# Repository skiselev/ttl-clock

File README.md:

# TTL Clock
74xx ICs Based Digital Clock

## Introduction
I got a bit tired from soldering SMD components, writing firmware, (and also observing people building vintage-looking Nixie clocks using modern microcontrollers). And recently when cleaning my parts boxes I found several 74LS47 7-segment decoders, some 74LS90 decade counters, and MAN1A 7-segment displays. So I thought, why not to build a nice little clock using these components.

## Assembly Instructions

[Assembly Instructions](Assembly_Instructions.md)

## Design Overview
Please refer to the schematic file in the Design Files section below.

The clock uses a 32768 Hz quartz crystal (X1) and 74HC4060 counter/divider IC (U1) to generate 2 Hz signal. This signal is divided further by 2 using a part of 74LS90 counter (U6). The obtained 1 Hz signal is fed to two 74LS90 counters (U11 and U12) that count seconds. The seconds reset circuit implemented using two 74LS00 NAND gates (U4A and U4B). This circuit resets both seconds and tens of seconds counters when they reach "60" or when "SECONDS" switch (SW1) is pressed, allowing seconds adjustment.

The most significant bit of tens of seconds counter is fed to the minutes counter implemented using two 74LS90 counters (U13 and U14) through a multiplexer built from three 74LS00 NAND gates (U2C, U2D, U4D). The multiplexer selects between this "one pulse per minute" signal and the 2 Hz signal allowing setting up minutes. Two additional 74LS00 NAND gates (U2A and U2B) implement an RS flip-flop used to de-bounce "MINUTES" switch (SW2). The tens of the minutes 74LS90 counter (U14) is wired so that it resets itself when it reaches count of "6", so that minutes wrap around at "60".

Similarly to minutes, the most significant bit of tens of minutes is fed to the hours counter implemented using two 74LS90 counters (U15 and U16) through a multiplexer built from three 74LS00 NAND gates (U3C, U3D, U4C). The multiplexer selects between this "one pulse per hour" signal and the 2 Hz signal allowing setting up hours. Two additional 74LS00 NAND gates (U3A and U3B) implement an RS flip-flop used to de-bounce "HOURS" switch (SW3). Both hours counters are wired in such a way that they will reset themselves once they reach the count of "24".

Six 74LS47 7-segment decoders (U5 - U10) are used to decode the binary outputs of the counters and 7-segment displays (U17 - U19) display the result in human readable 24-hours time format.

## Design Files

[Schematic - Version 1.1](KiCad/TTL_Clock-Schematic-1.1.pdf)

[Board - Version 1.1](KiCad/TTL_Clock-Board-1.1.pdf)

## Bill of Materials

[TTL Clock V1.1 project on Mouser.com](https://www.mouser.com/ProjectManager/ProjectDetail.aspx?AccessID=75baf81884) - View and order all components except of the PCB.

[TTL Clock Version 1.1 project on OSH Park](https://oshpark.com/shared_projects/GOxwvQh1) - Order PCBs.

Component type     | Reference | Description                                 | Quantity | Possible sources and notes
------------------ | --------- | ------------------------------------------- | -------- | --------------------------
PCB                |           | TTL Clock V1.1 Printed Circuit Board        | 1        | Order from [OSH Park](https://oshpark.com/shared_projects/GOxwvQh1) or another PCB manufacturer using provided KiCad or Gerber files
Stand              |           | 3D printed stand for the clock              | 1        | (Optional) Print on a 3D printer using [stand.stl](printed_parts/stand.stl). Thanks to Michael K. for designing this stand.
Screw              |           | M3 x 6mm screw                              | 2        | (Optional)
Capacitor          | C1 - C16  | 0.1uF, 50V, multilayer ceramic capacitor, axial | 16   | Mouser: [594-A104K15X7RF5UAA](https://www.mouser.com/ProductDetail/594-A104K15X7RF5UAA)
Capacitor          | C17       | 100uF, 25V, electrolytic capacitor, radial, 6.3 mm diameter | 1 | Mouser: [710-860040473003](https://www.mouser.com/ProductDetail/710-860040473003)
Capacitor          | C18       | 12pF, 50V, multilayer ceramic capacitor, 5.08 mm lead spacing | 1 | Mouser: [810-FK28C0G1H120J](https://www.mouser.com/ProductDetail/810-FK28C0G1H120J)
Trimmer Capacitor  | C19       | 5-30pF, trimmer capacitor, 5 mm lead spacing | 1       | Mouser: [659-GKG20015](https://www.mouser.com/ProductDetail/659-GKG20015)
LED                | D1 - D4   | 3 mm LED, same color as U17 - U19            | 4       | Mouser: [859-LTL-4221](https://www.mouser.com/ProductDetail/859-LTL-4221) (red, 623 nm) [859-LTL-4211](https://www.mouser.com/ProductDetail/859-LTL-4211) (red, 697 nm, 2.5 mcd), [859-LTL-4231](https://www.mouser.com/ProductDetail/859-LTL-4231) (green, 565 nm)
Connector          | P1        | DC Power Jack                               | 1        | Mouser: [806-KLDX-0202-A](https://www.mouser.com/ProductDetail/806-KLDX-0202-A)
Resistor           | R1 - R5   | 4.7 kOhm, 1/4 W                             | 5        | Mouser: [588-OK4725E-R52](https://www.mouser.com/ProductDetail/588-OK4725E-R52), [603-MFR25SFRF52-4K7](https://www.mouser.com/ProductDetail/603-MFR25SFRF52-4K7)
Resistor           | R6        | 330 kOhm, 1/4 W                             | 1        | Mouser: [588-OK3345E-R52](https://www.mouser.com/ProductDetail/588-OK3345E-R52)
Resistor           | R7        | 15 MOhm, 1/4 W                              | 1        | Mouser: [660-CF1/4C156J](https://www.mouser.com/ProductDetail/660-CF1-4C156J)
Resistor Array     | RR1 - RR6 | 470 Ohm, 8 isolated resistors, 16 pin DIP   | 6        | Mouser: [652-4116R-1LF-470](https://www.mouser.com/ProductDetail/652-4116R-1LF-470), [652-4116R-1-470](https://www.mouser.com/ProductDetail/652-4116R-1-470), or 46 x 470 ohm discrete resistors
Switch             | SW1 - SW3 | SPDT momentary switch, Omron D2F            | 3        | Mouser: [612-SS0750301F040P1A](https://www.mouser.com/ProductDetail/612-SS0750301F040P1A), [653-D2F-01L](https://www.mouser.com/ProductDetail/653-D2F-01L)
Integrated Circuit | U1        | 14-stage binary counter with oscillator, 74HC4060 | 1  | Mouser: [595-SN74HC4060N](https://www.mouser.com/ProductDetail/595-SN74HC4060N), [595-CD74HCT4060E](https://www.mouser.com/ProductDetail/595-CD74HCT4060E), [595-CD74HC4060E](https://www.mouser.com/ProductDetail/595-CD74HC4060E)
Integrated Circuit | U2 - U4   | Quad 4-input NAND gate, 74LS00              | 3        | Mouser: [595-SN74LS00N](https://www.mouser.com/ProductDetail/595-SN74LS00N), [595-SN74LS00NE4](https://www.mouser.com/ProductDetail/595-SN74LS00NE4)
Integrated Circuit | U5 - U10  | BCD to 7-segment decoder, 74LS47 or 74LS247 | 6        | Mouser: [595-SN74LS47N](https://www.mouser.com/ProductDetail/595-SN74LS47N), [595-SN74LS47NE4](https://www.mouser.com/ProductDetail/SN74LS47NE4), [595-SN74LS247N](https://www.mouser.com/ProductDetail/595-SN74LS247N), [595-SN74LS247NE4](https://www.mouser.com/ProductDetail/595-SN74LS247NE4)
Integrated Circuit | U11 - U16 | Decade counter, 74LS90                      | 6        | Mouser: [595-SN74LS90N](https://www.mouser.com/ProductDetail/595-SN74LS90N), [595-SN74LS90NE4](https://www.mouser.com/ProductDetail/595-SN74LS90NE4)
LED Display        | U17 - U19 | 7-segment LED display, 2 digits, common anode | 3      | Mouser: [859-LTD-6910HR](https://www.mouser.com/ProductDetail/859-LTD-6910HR) (red, 623 nm), [859-LTD-6410G](https://www.mouser.com/ProductDetail/859-LTD-6410G) (green, 569 nm)
Crystal Resonator  | X1        | 32768 Hz, 12.5pF load capacitance, tuning fork | 1     | Mouser: [695-CFS-20632768EZBB](https://www.mouser.com/ProductDetail/695-CFS-20632768EZBB), [815-AB26T-32.768KHZ](https://www.mouser.com/ProductDetail/815-AB26T-32.768KHZ)
Power Supply       |           | 5 V, 550 mA                                 | 1        | Mouser: [490-SWI3-5-N-P5](https://www.mouser.com/ProductDetail/490-SWI3-5-N-P5) (US plug), [490-SWI3-5-E-P5](https://www.mouser.com/ProductDetail/490-SWI3-5-E-P5) (EU plug)

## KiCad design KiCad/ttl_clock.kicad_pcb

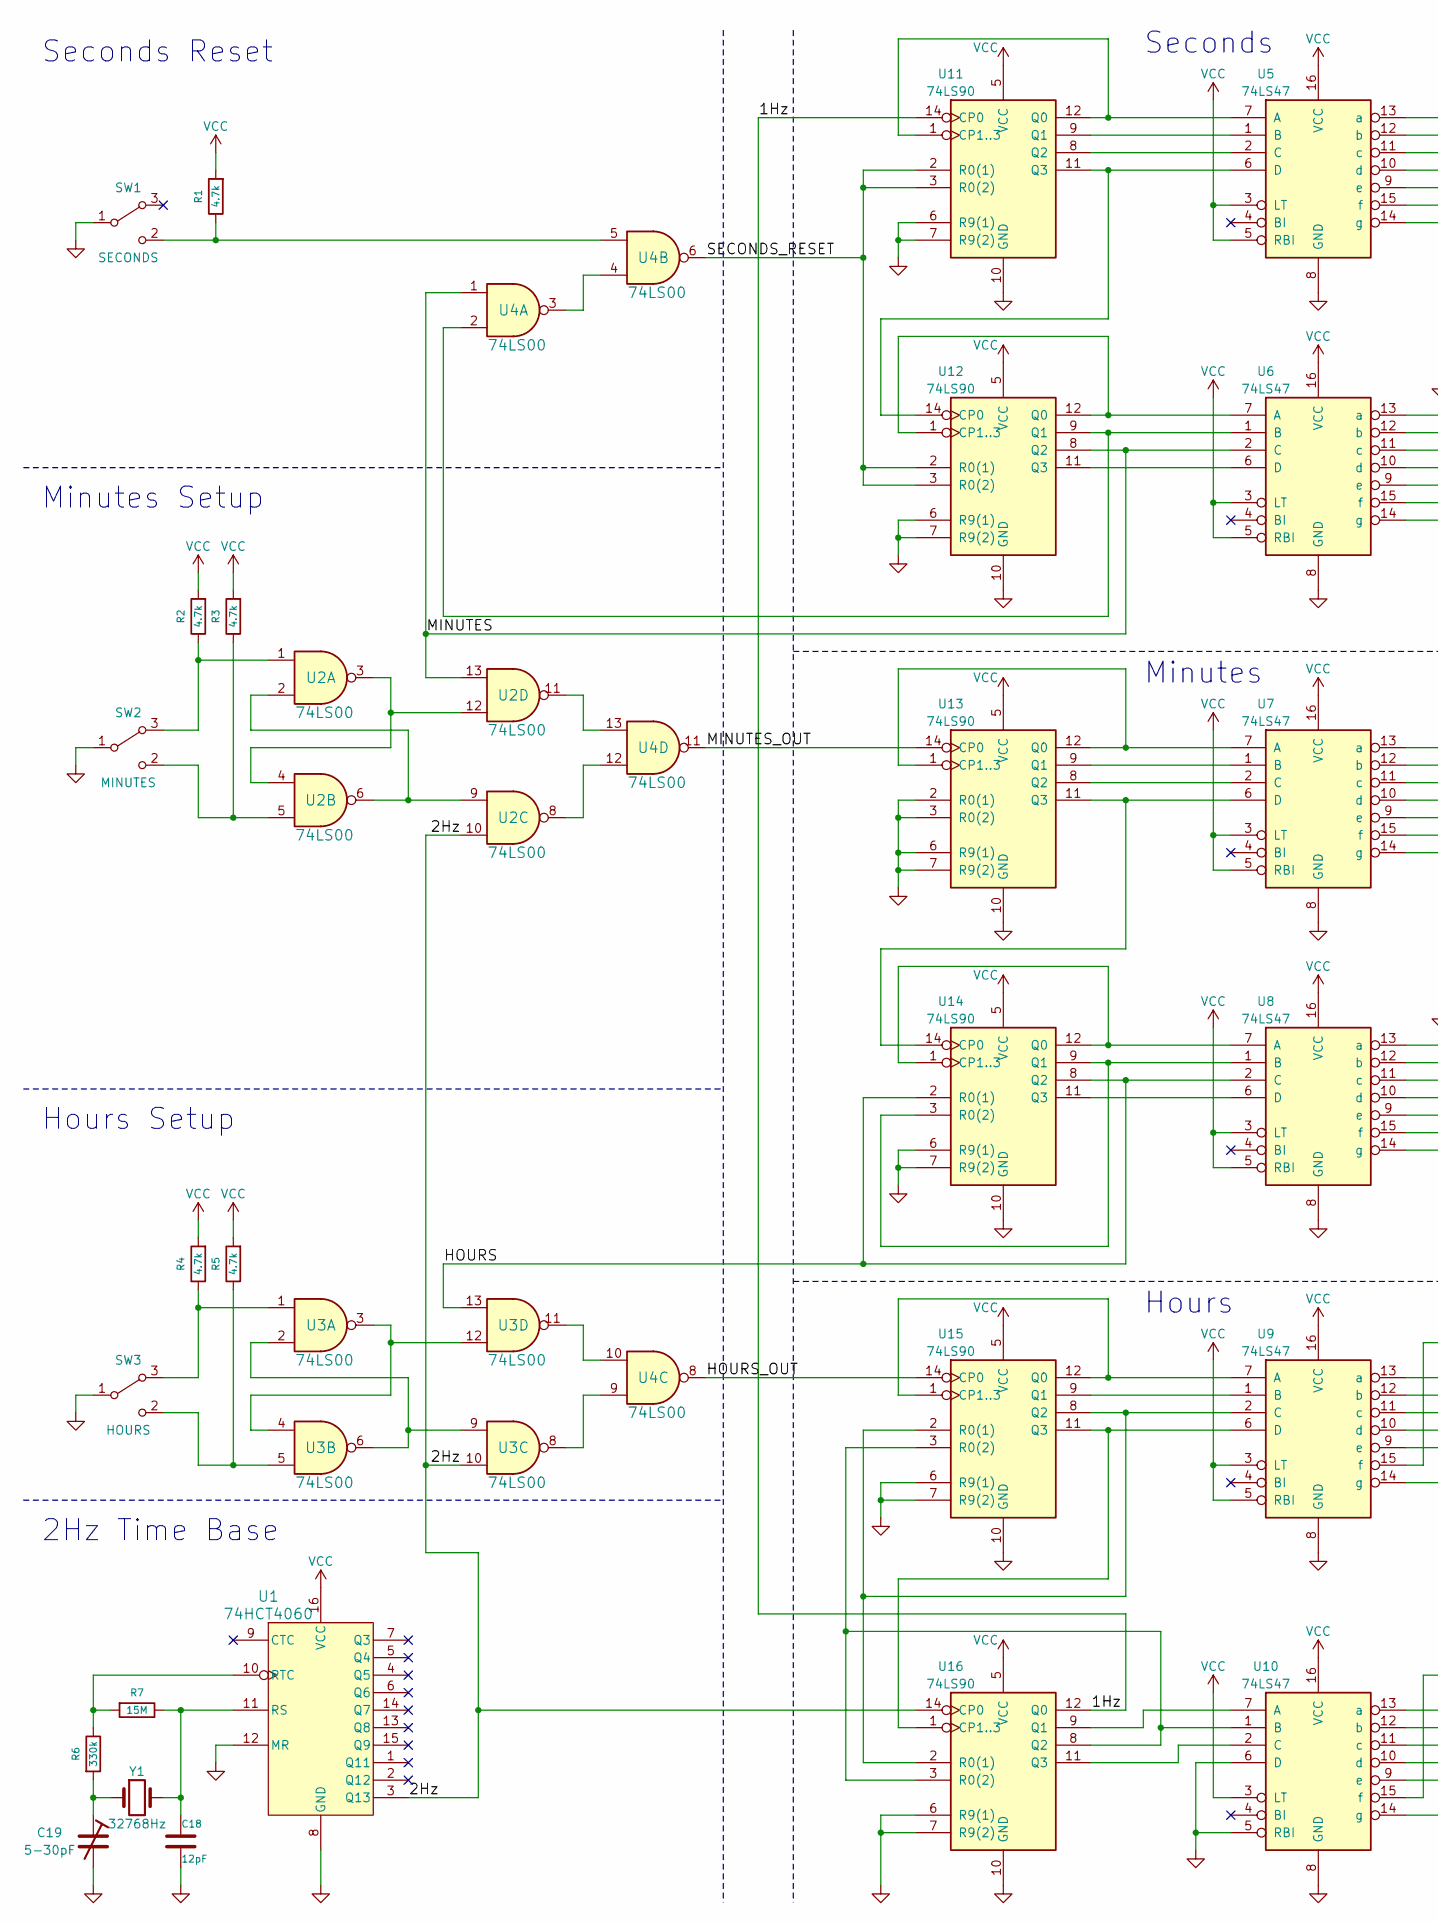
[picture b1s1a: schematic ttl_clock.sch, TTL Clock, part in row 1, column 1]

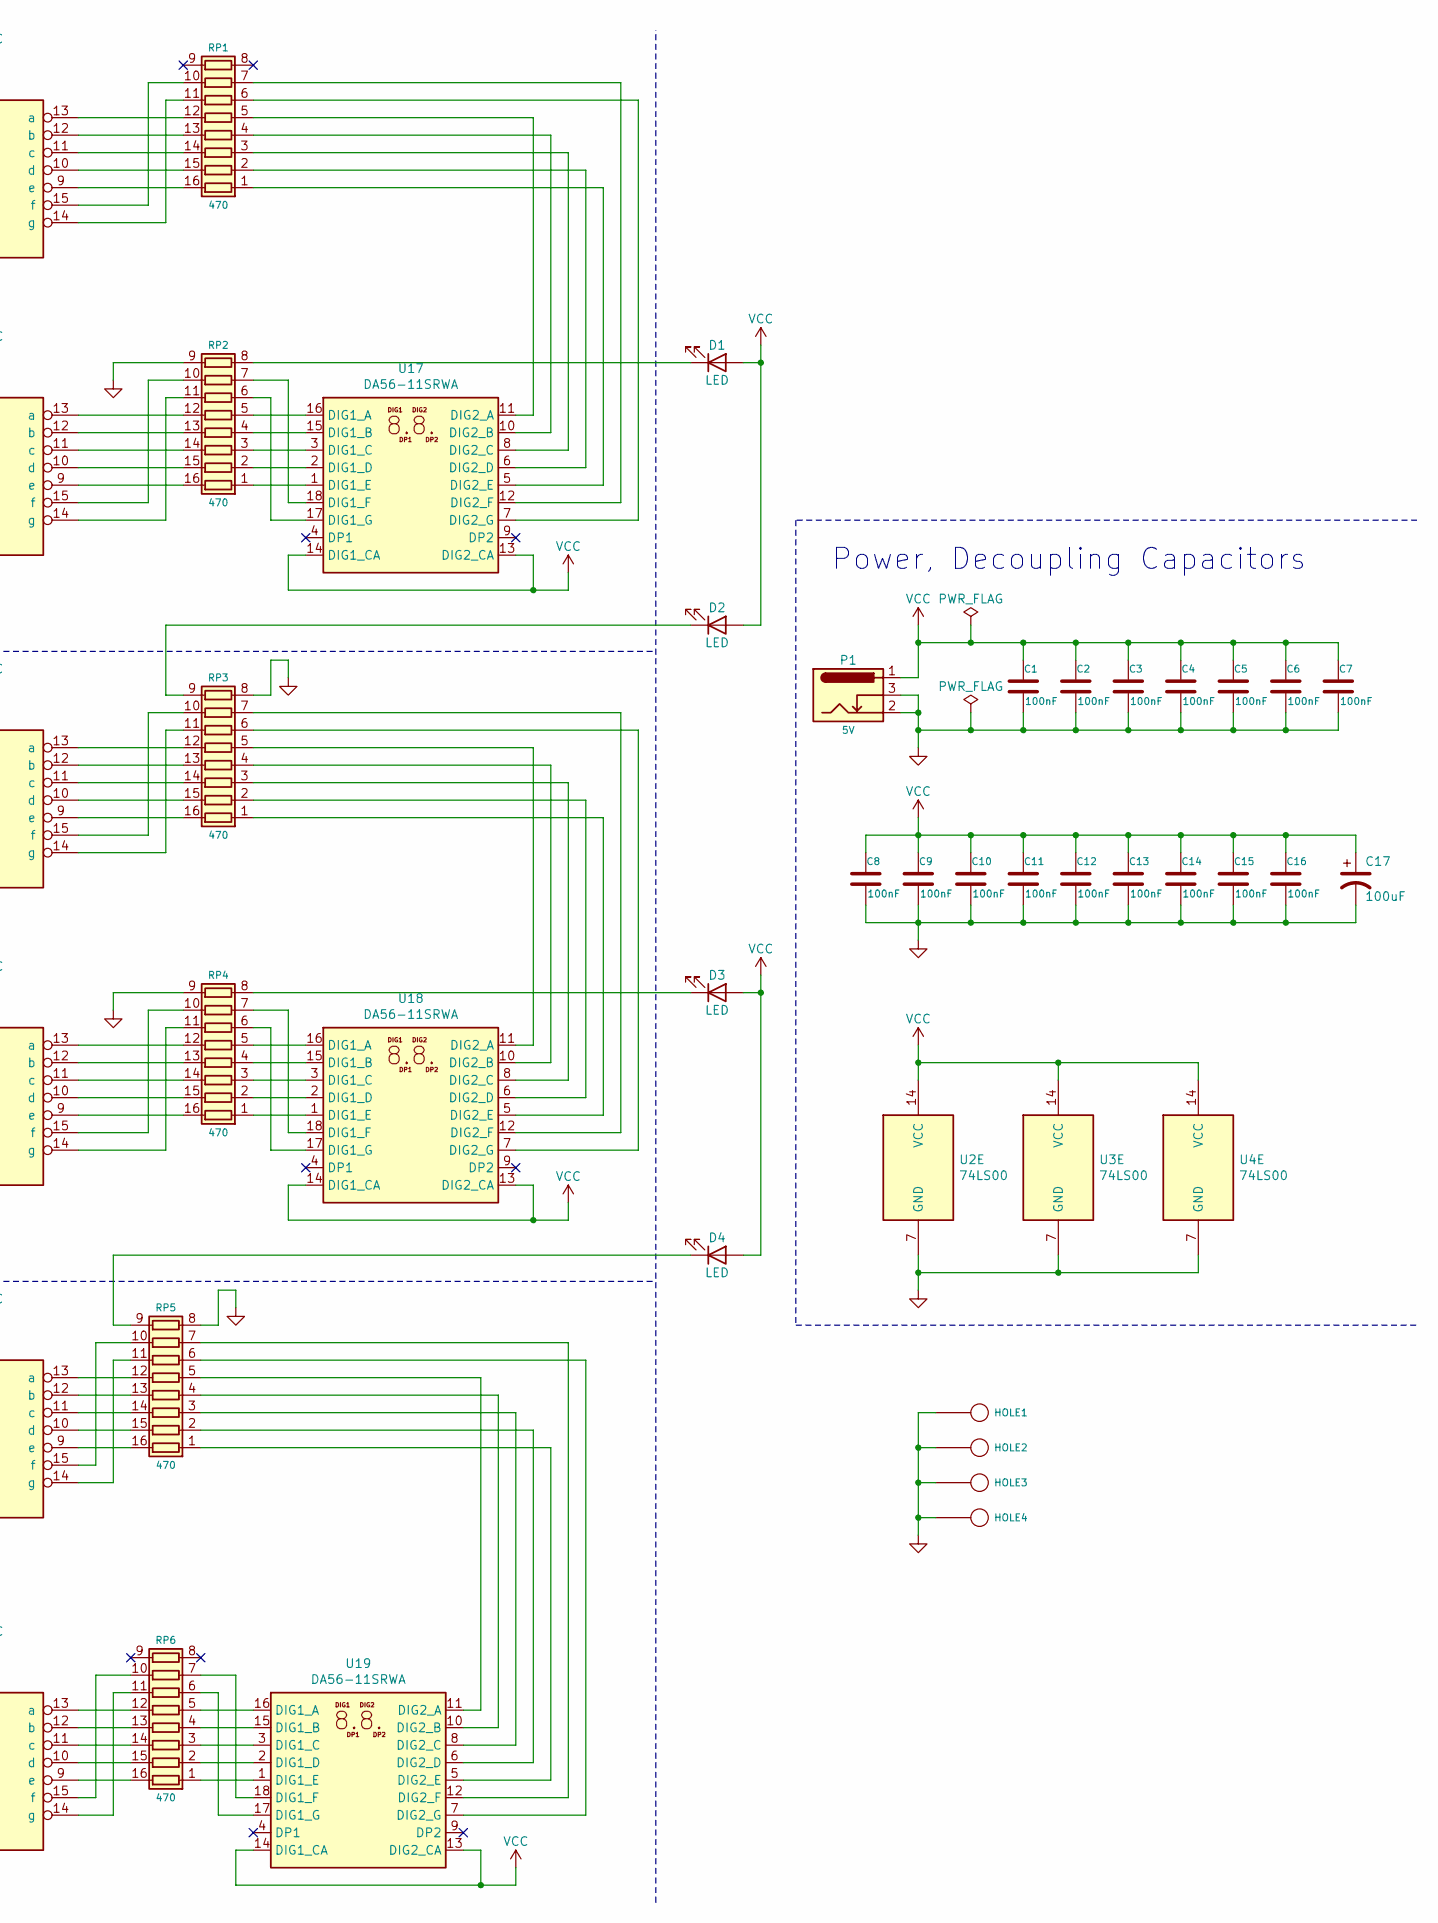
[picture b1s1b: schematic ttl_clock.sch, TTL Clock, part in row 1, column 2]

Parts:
C1, C2, C3, C4, C5, C6, C7, C8, C9, C10, C11, C12, C13, C14, C15, C16: 100nF; Cap_Cer_762
C17: 100uF; CP_Radial_D6.3mm_P2.50mm
C18: 12pF; Cap_Cer_508
C19: 5-30pF; C_Trim_Murata
D1, D2, D3, D4: LED; LED_D3.0mm_FlatTop
HOLE1, HOLE2, HOLE3, HOLE4: CONN_1; MountingHole_3mm_Pad_Via
P1: 5V; Conn_Power_Jack_Circular_Pads
R1, R2, R3, R4, R5: 4.7k; Res_762
R6: 330k; Res_762
R7: 15M; Res_762
RP1, RP2, RP3, RP4, RP5, RP6: 470; IC_DIP16_300
SW1: SECONDS; Switch_SPDP_D2F
SW2: MINUTES; Switch_SPDP_D2F
SW3: HOURS; Switch_SPDP_D2F
U1: 74HCT4060; IC_DIP16_300
U2, U3, U4: 74LS00; IC_DIP14_300
U5, U6, U7, U8, U9, U10: 74LS47; IC_DIP16_300
U11, U12, U13, U14, U15, U16: 74LS90; IC_DIP14_300
U17, U18, U19: DA56-11SRWA; DA56-11SURKWA
Y1: 32768Hz; Crystal_32K_Horiz

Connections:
/1Hz: U11.14 (CP0), U16.12 (Q0)
/2Hz: U1.3 (Q13), U2.10, U3.10, U16.14 (CP0)
/HOURS: U3.13, U8.2 (C), U14.2 (R0(1)), U14.8 (Q2)
/HOURS_OUT: U4.8, U15.14 (CP0)
/MINUTES: U2.13, U4.1, U6.2 (C), U12.8 (Q2)
/MINUTES_OUT: U4.11, U13.14 (CP0)
/SECONDS_RESET: U4.6, U11.2 (R0(1)), U11.3 (R0(2)), U12.2 (R0(1)), U12.3 (R0(2))
GND: C1.2, C2.2, C3.2, C4.2, C5.2, C6.2, C7.2, C8.2, C9.2, C10.2, C11.2, C12.2, C13.2, C14.2, C15.2, C16.2, C17.2, C18.2, C19.2, HOLE1.1, HOLE2.1, HOLE3.1, HOLE4.1, P1.2, P1.3, RP2.9 (R8.2), RP3.8 (R8.1), RP4.9 (R8.2), RP5.8 (R8.1), SW1.1 (B), SW2.1 (B), SW3.1 (B), U1.8 (GND), U1.12 (MR), U2.7 (GND), U3.7 (GND), U4.7 (GND), U5.8 (GND), U6.8 (GND), U7.8 (GND), U8.8 (GND), U9.8 (GND), U10.5 (RBI), U10.6 (D), U10.8 (GND), U11.6 (R9(1)), U11.7 (R9(2)), U11.10 (GND), U12.6 (R9(1)), U12.7 (R9(2)), U12.10 (GND), U13.2 (R0(1)), U13.3 (R0(2)), U13.6 (R9(1)), U13.7 (R9(2)), U13.10 (GND), U14.6 (R9(1)), U14.7 (R9(2)), U14.10 (GND), U15.6 (R9(1)), U15.7 (R9(2)), U15.10 (GND), U16.6 (R9(1)), U16.7 (R9(2)), U16.10 (GND)
unnamed: C18.1, R7.1, U1.11 (RS), Y1.2
unnamed: C19.1, R6.2, Y1.1
unnamed: D1.1 (K), RP2.8 (R8.1)
unnamed: D2.1 (K), RP3.9 (R8.2)
unnamed: D3.1 (K), RP4.8 (R8.1)
unnamed: D4.1 (K), RP5.9 (R8.2)
unnamed: R1.1, SW1.2 (C), U4.5
unnamed: R2.1, SW2.3 (A), U2.1
unnamed: R3.1, SW2.2 (C), U2.5
unnamed: R4.1, SW3.3 (A), U3.1
unnamed: R5.1, SW3.2 (C), U3.5
unnamed: R6.1, R7.2, U1.10 (RTC)
unnamed: RP1.1 (R1.1), U17.5 (DIG2_E)
unnamed: RP1.2 (R2.1), U17.6 (DIG2_D)
unnamed: RP1.3 (R3.1), U17.8 (DIG2_C)
unnamed: RP1.4 (R4.1), U17.10 (DIG2_B)
unnamed: RP1.5 (R5.1), U17.11 (DIG2_A)
unnamed: RP1.6 (R6.1), U17.7 (DIG2_G)
unnamed: RP1.7 (R7.1), U17.12 (DIG2_F)
unnamed: RP1.10 (R7.2), U5.15 (f)
unnamed: RP1.11 (R6.2), U5.14 (g)
unnamed: RP1.12 (R5.2), U5.13 (a)
unnamed: RP1.13 (R4.2), U5.12 (b)
unnamed: RP1.14 (R3.2), U5.11 (c)
unnamed: RP1.15 (R2.2), U5.10 (d)
unnamed: RP1.16 (R1.2), U5.9 (e)
unnamed: RP2.1 (R1.1), U17.1 (DIG1_E)
unnamed: RP2.2 (R2.1), U17.2 (DIG1_D)
unnamed: RP2.3 (R3.1), U17.3 (DIG1_C)
unnamed: RP2.4 (R4.1), U17.15 (DIG1_B)
unnamed: RP2.5 (R5.1), U17.16 (DIG1_A)
unnamed: RP2.6 (R6.1), U17.17 (DIG1_G)
unnamed: RP2.7 (R7.1), U17.18 (DIG1_F)
unnamed: RP2.10 (R7.2), U6.15 (f)
unnamed: RP2.11 (R6.2), U6.14 (g)
unnamed: RP2.12 (R5.2), U6.13 (a)
unnamed: RP2.13 (R4.2), U6.12 (b)
unnamed: RP2.14 (R3.2), U6.11 (c)
unnamed: RP2.15 (R2.2), U6.10 (d)
unnamed: RP2.16 (R1.2), U6.9 (e)
unnamed: RP3.1 (R1.1), U18.5 (DIG2_E)
unnamed: RP3.2 (R2.1), U18.6 (DIG2_D)
unnamed: RP3.3 (R3.1), U18.8 (DIG2_C)
unnamed: RP3.4 (R4.1), U18.10 (DIG2_B)
unnamed: RP3.5 (R5.1), U18.11 (DIG2_A)
unnamed: RP3.6 (R6.1), U18.7 (DIG2_G)
unnamed: RP3.7 (R7.1), U18.12 (DIG2_F)
unnamed: RP3.10 (R7.2), U7.15 (f)
unnamed: RP3.11 (R6.2), U7.14 (g)
unnamed: RP3.12 (R5.2), U7.13 (a)
unnamed: RP3.13 (R4.2), U7.12 (b)
unnamed: RP3.14 (R3.2), U7.11 (c)
unnamed: RP3.15 (R2.2), U7.10 (d)
unnamed: RP3.16 (R1.2), U7.9 (e)
unnamed: RP4.1 (R1.1), U18.1 (DIG1_E)
unnamed: RP4.2 (R2.1), U18.2 (DIG1_D)
unnamed: RP4.3 (R3.1), U18.3 (DIG1_C)
unnamed: RP4.4 (R4.1), U18.15 (DIG1_B)
unnamed: RP4.5 (R5.1), U18.16 (DIG1_A)
unnamed: RP4.6 (R6.1), U18.17 (DIG1_G)
unnamed: RP4.7 (R7.1), U18.18 (DIG1_F)
unnamed: RP4.10 (R7.2), U8.15 (f)
unnamed: RP4.11 (R6.2), U8.14 (g)
unnamed: RP4.12 (R5.2), U8.13 (a)
unnamed: RP4.13 (R4.2), U8.12 (b)
unnamed: RP4.14 (R3.2), U8.11 (c)
unnamed: RP4.15 (R2.2), U8.10 (d)
unnamed: RP4.16 (R1.2), U8.9 (e)
unnamed: RP5.1 (R1.1), U19.5 (DIG2_E)
unnamed: RP5.2 (R2.1), U19.6 (DIG2_D)
unnamed: RP5.3 (R3.1), U19.8 (DIG2_C)
unnamed: RP5.4 (R4.1), U19.10 (DIG2_B)
unnamed: RP5.5 (R5.1), U19.11 (DIG2_A)
unnamed: RP5.6 (R6.1), U19.7 (DIG2_G)
unnamed: RP5.7 (R7.1), U19.12 (DIG2_F)
unnamed: RP5.10 (R7.2), U9.15 (f)
unnamed: RP5.11 (R6.2), U9.14 (g)
unnamed: RP5.12 (R5.2), U9.13 (a)
unnamed: RP5.13 (R4.2), U9.12 (b)
unnamed: RP5.14 (R3.2), U9.11 (c)
unnamed: RP5.15 (R2.2), U9.10 (d)
unnamed: RP5.16 (R1.2), U9.9 (e)
unnamed: RP6.1 (R1.1), U19.1 (DIG1_E)
unnamed: RP6.2 (R2.1), U19.2 (DIG1_D)
unnamed: RP6.3 (R3.1), U19.3 (DIG1_C)
unnamed: RP6.4 (R4.1), U19.15 (DIG1_B)
unnamed: RP6.5 (R5.1), U19.16 (DIG1_A)
unnamed: RP6.6 (R6.1), U19.17 (DIG1_G)
unnamed: RP6.7 (R7.1), U19.18 (DIG1_F)
unnamed: RP6.10 (R7.2), U10.15 (f)
unnamed: RP6.11 (R6.2), U10.14 (g)
unnamed: RP6.12 (R5.2), U10.13 (a)
unnamed: RP6.13 (R4.2), U10.12 (b)
unnamed: RP6.14 (R3.2), U10.11 (c)
unnamed: RP6.15 (R2.2), U10.10 (d)
unnamed: RP6.16 (R1.2), U10.9 (e)
unnamed: U2.2, U2.6, U2.9
unnamed: U2.8, U4.12
unnamed: U2.11, U4.13
unnamed: U2.3, U2.4, U2.12
unnamed: U3.2, U3.6, U3.9
unnamed: U3.8, U4.9
unnamed: U3.11, U4.10
unnamed: U3.3, U3.4, U3.12
unnamed: U4.3, U4.4
unnamed: U10.1 (B), U15.3 (R0(2)), U16.3 (R0(2)), U16.8 (Q2)
unnamed: U10.2 (C), U16.11 (Q3)
unnamed: U10.7 (A), U16.9 (Q1)
unnamed: U5.7 (A), U11.1 (CP1..3), U11.12 (Q0)
unnamed: U5.2 (C), U11.8 (Q2)
unnamed: U5.1 (B), U11.9 (Q1)
unnamed: U5.6 (D), U11.11 (Q3), U12.14 (CP0)
unnamed: U6.7 (A), U12.1 (CP1..3), U12.12 (Q0)
unnamed: U4.2, U6.1 (B), U12.9 (Q1)
unnamed: U6.6 (D), U12.11 (Q3)
unnamed: U7.7 (A), U13.1 (CP1..3), U13.12 (Q0)
unnamed: U7.2 (C), U13.8 (Q2)
unnamed: U7.1 (B), U13.9 (Q1)
unnamed: U7.6 (D), U13.11 (Q3), U14.14 (CP0)
unnamed: U8.7 (A), U14.1 (CP1..3), U14.12 (Q0)
unnamed: U8.1 (B), U14.3 (R0(2)), U14.9 (Q1)
unnamed: U8.6 (D), U14.11 (Q3)
unnamed: U9.7 (A), U15.1 (CP1..3), U15.12 (Q0)
unnamed: U9.2 (C), U15.2 (R0(1)), U15.8 (Q2), U16.2 (R0(1))
unnamed: U9.1 (B), U15.9 (Q1)
unnamed: U9.6 (D), U15.11 (Q3), U16.1 (CP1..3)
VCC: C1.1, C2.1, C3.1, C4.1, C5.1, C6.1, C7.1, C8.1, C9.1, C10.1, C11.1, C12.1, C13.1, C14.1, C15.1, C16.1, C17.1, D1.2 (A), D2.2 (A), D3.2 (A), D4.2 (A), P1.1, R1.2, R2.2, R3.2, R4.2, R5.2, U1.16 (VCC), U2.14 (VCC), U3.14 (VCC), U4.14 (VCC), U5.3 (LT), U5.5 (RBI), U5.16 (VCC), U6.3 (LT), U6.5 (RBI), U6.16 (VCC), U7.3 (LT), U7.5 (RBI), U7.16 (VCC), U8.3 (LT), U8.5 (RBI), U8.16 (VCC), U9.3 (LT), U9.5 (RBI), U9.16 (VCC), U10.3 (LT), U10.16 (VCC), U11.5 (VCC), U12.5 (VCC), U13.5 (VCC), U14.5 (VCC), U15.5 (VCC), U16.5 (VCC), U17.13 (DIG2_CA), U17.14 (DIG1_CA), U18.13 (DIG2_CA), U18.14 (DIG1_CA), U19.13 (DIG2_CA), U19.14 (DIG1_CA)

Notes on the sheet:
Seconds
Minutes
Power, Decoupling Capacitors
Hours Setup
Minutes Setup
Seconds Reset
Hours
2Hz Time Base

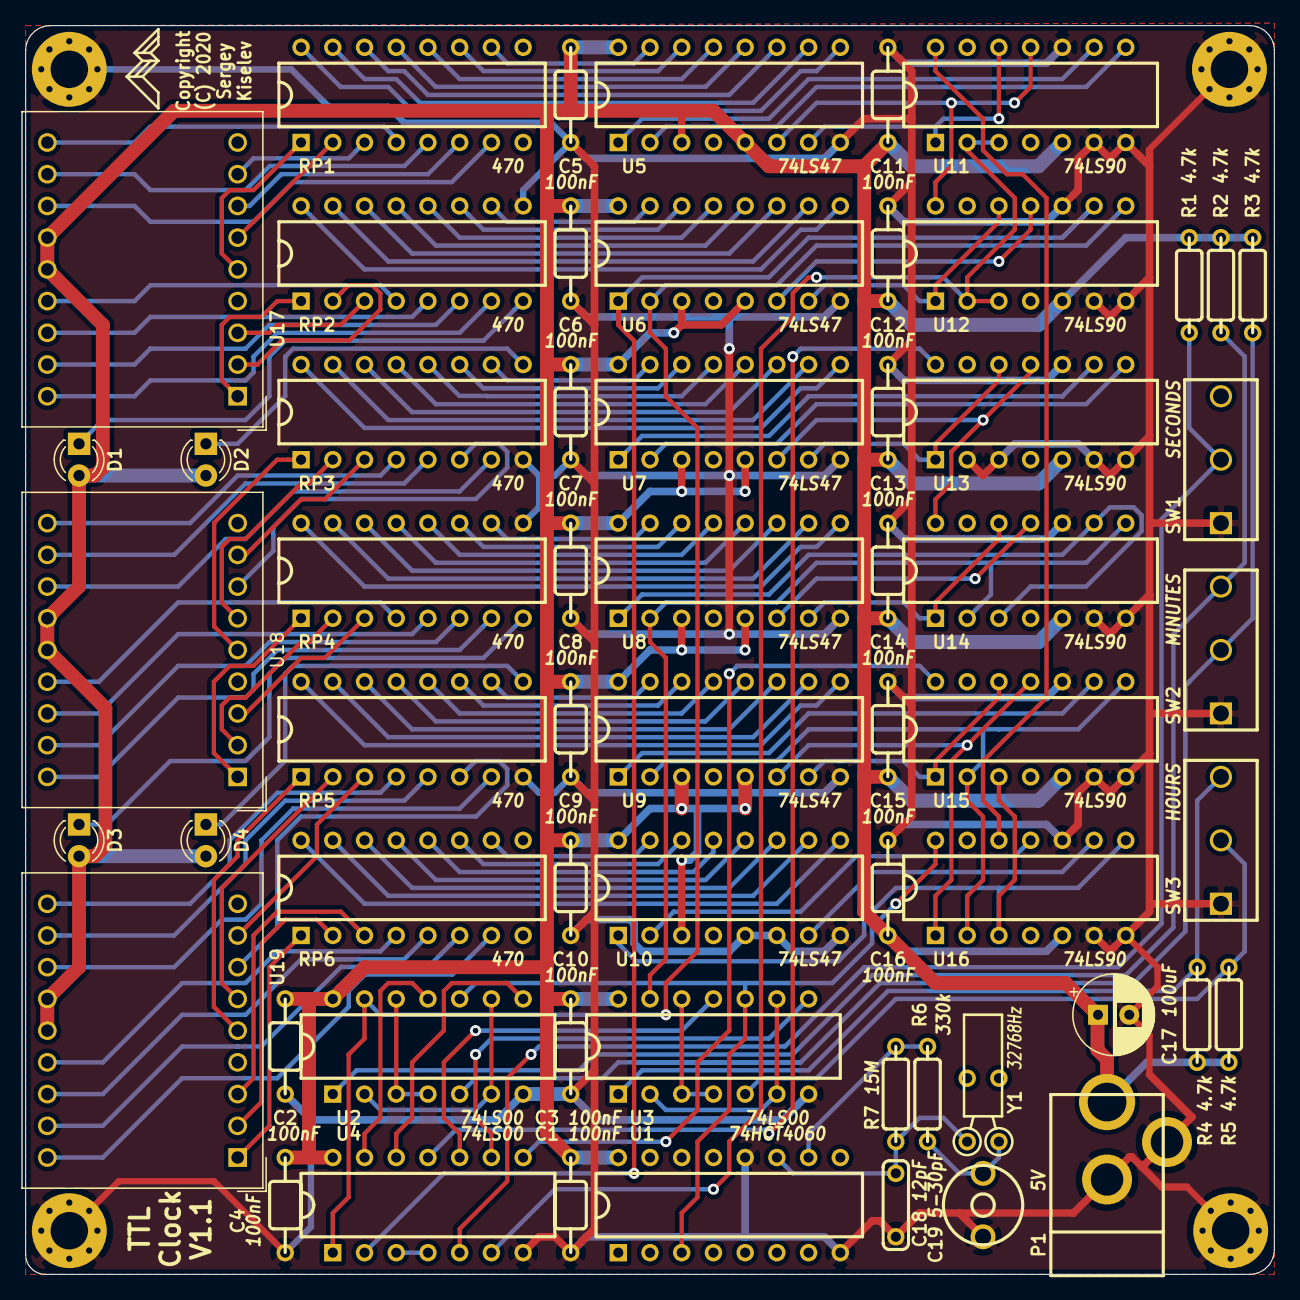
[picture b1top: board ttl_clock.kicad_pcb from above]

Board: 2 copper layers, 100.0 x 100.0 mm, 64 parts (0 on the bottom side), 135 nets.

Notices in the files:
KiCad/led_clock.kicad_pcb:
(C) 2015
KiCad/ttl_clock.kicad_pcb:
License: GPLv3
(C) 2020
